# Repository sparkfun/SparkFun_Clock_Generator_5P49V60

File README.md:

SparkFun Clock Generator 5P49V60
========================================

[*SparkFun Clock Generator 5P49V60 (BOB-15734)*](https://www.sparkfun.com/products/15734)

The SparkFun Clock Generator 5P49V60 breakout board offers a wide range of customizable frequencies in a wide range 
of different signal types using a single reference clock. Four (single output) clock outputs can generate frequencies 
from 1MHz-200MHz and eight (differential output) clock outputs can generate frequencies from 1MHz-350MHz. The frequency's 
many properties can be manipulated in code via I2C using the SparkFun Arduino Library. The SparkFun Clock Generator also 
has four banks of programmable memory for the time when it's ready to sit on its' own within the project without a microcontroller.

Repository Contents
-------------------

* **/Hardware** - Eagle design files (.brd, .sch)
* **/Production** - Production panel files (.brd)
* **/Documentation** - Datasheet for the 5P49V60

Documentation
--------------
* **[Library](https://github.com/sparkfun/SparkFun_Clock_Generator_5P49V60_Arduino_Library)** - Arduino Library for the SparkFun Clock Generator 5P49V60
* **[Hookup Guide](https://learn.sparkfun.com/tutorials/sparkfun-clock-generator-5p49v60-qwiic-hookup-guide)** - Hookup Guide for the SparkFun Clock Generator 5P49V60
* **[SparkFun Fritzing repo](https://github.com/sparkfun/Fritzing_Parts)** - Fritzing diagrams for SparkFun products.

License Information
-------------------

This product is _**open source**_! 

Please review the LICENSE.md file for license information. 

If you have any questions or concerns on licensing, please contact technical support on our [SparkFun forums](https://forum.sparkfun.com/viewforum.php?f=152).

Distributed as-is; no warranty is given.

- Your friends at SparkFun.

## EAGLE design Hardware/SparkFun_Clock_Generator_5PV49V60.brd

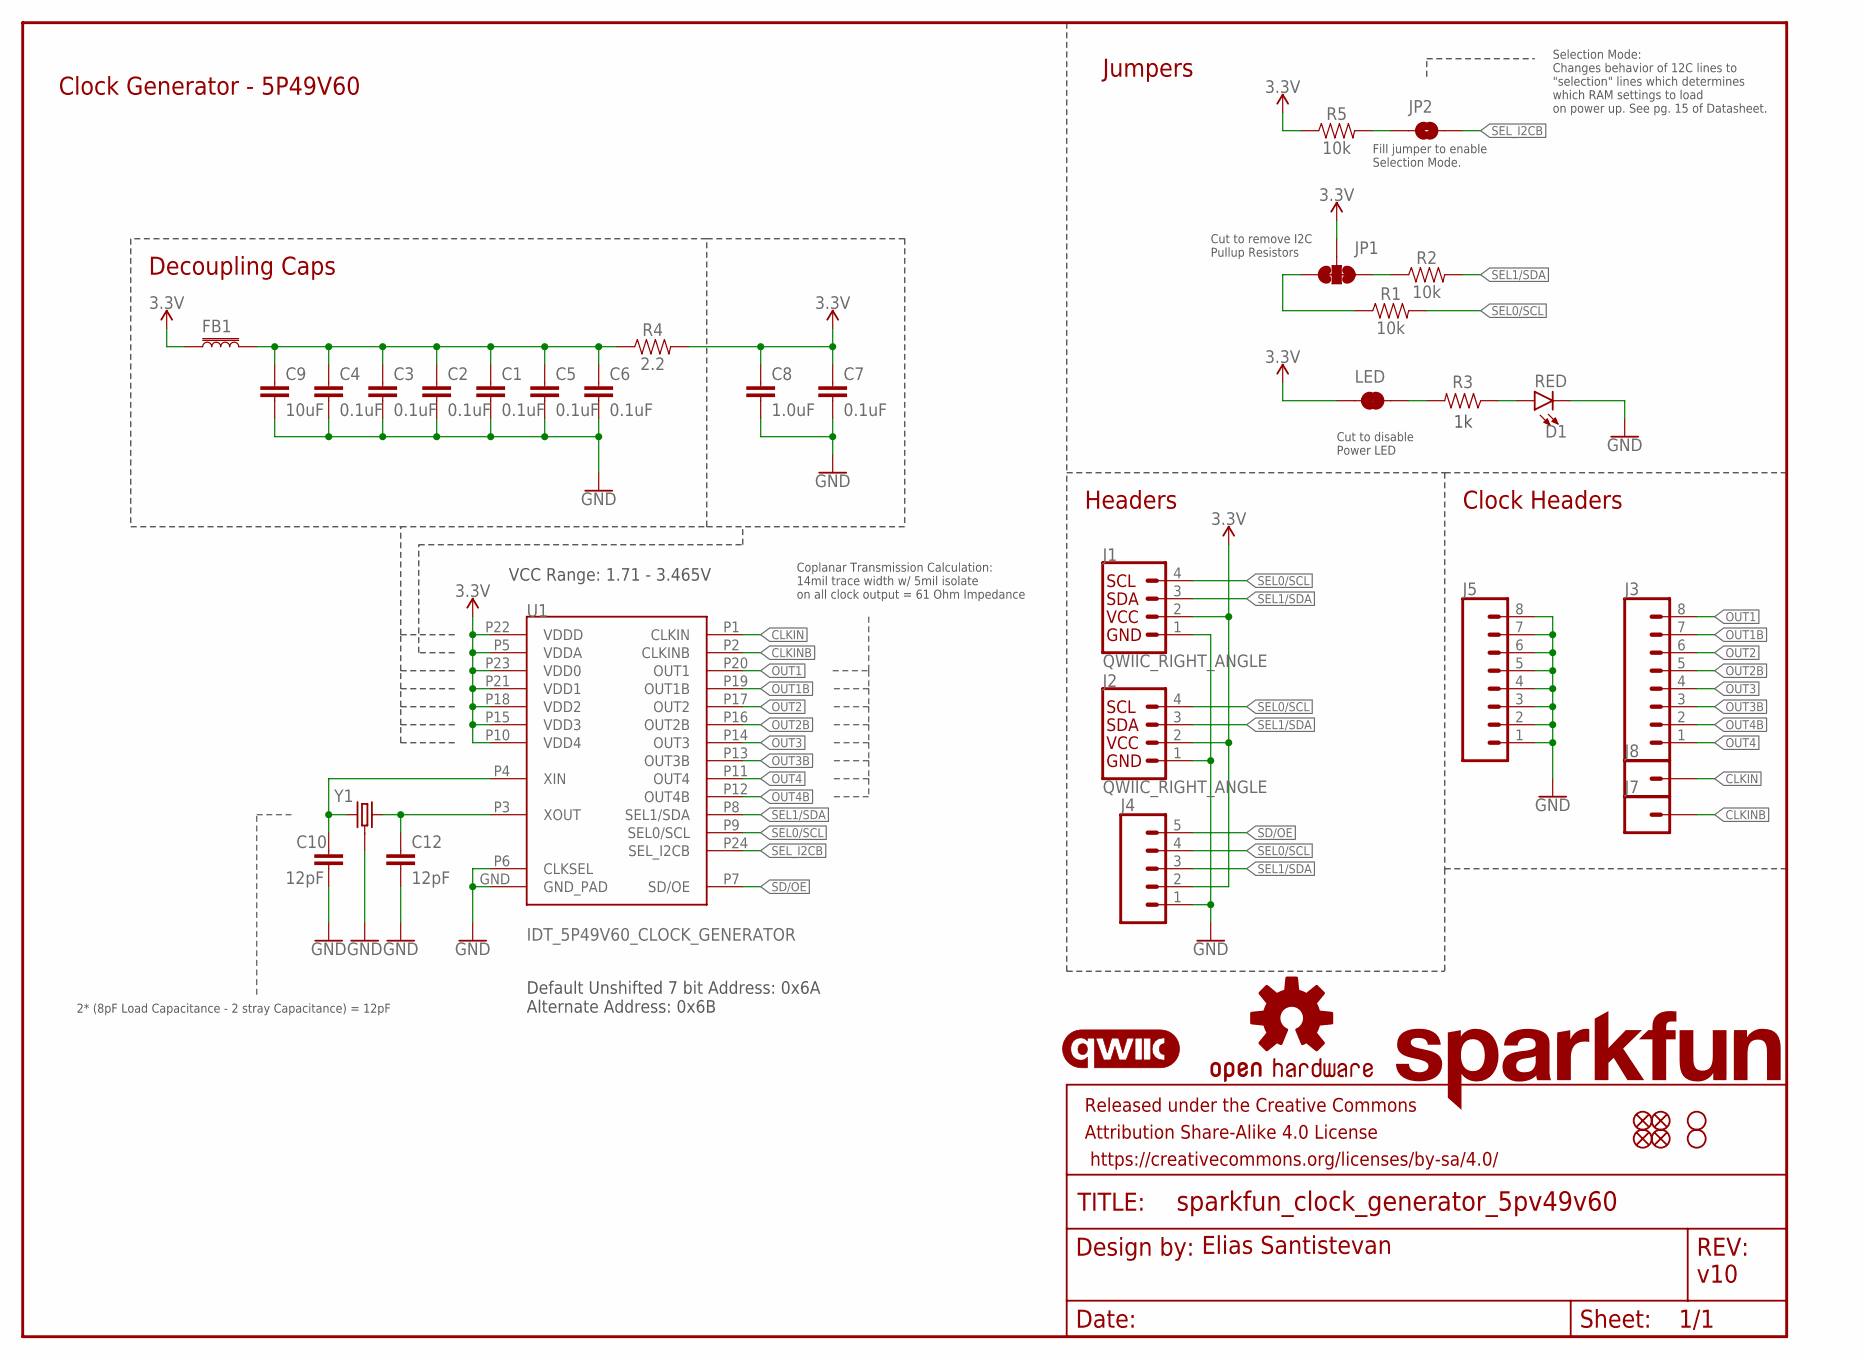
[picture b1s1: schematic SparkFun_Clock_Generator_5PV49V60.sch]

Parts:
C1, C2, C3, C4, C5, C6, C7: 0.1uF; 0402
C8: 1.0uF; 0402
C9: 10uF; 0603
C10, C12: 12pF; 0402
D1: RED; LED-0603
FB1: FERRITE_BEAD-120_OHM-0402; 0402
FD1, FD2, FD3, FD4: FIDUCIALUFIDUCIAL; FIDUCIAL-MICRO
FRAME1: FRAME-LETTER; CREATIVE_COMMONS
H1, H2: STAND-OFFTIGHT; STAND-OFF-TIGHT
J1, J2: QWIIC_RIGHT_ANGLE; JST04_1MM_RA
J3, J5: CONN_08NO_SILK_FEMALE_PTH; 1X08_NO_SILK
J4: CONN_05NO_SILK; 1X05_NO_SILK
J7, J8: CONN_01PTH_NO_SILK_SMALL; 1X01_SMALL
JP1: JUMPER-SMT_3_2-NC_TRACE_SILK; SMT-JUMPER_3_2-NC_TRACE_SILK
JP2: JUMPER-SMT_2_NO_SILK; SMT-JUMPER_2_NO_SILK
LED: JUMPER-SMT_2_NC_TRACE_SILK; SMT-JUMPER_2_NC_TRACE_SILK
LOGO1: SFE_LOGO_NAME.1_INCH; SFE_LOGO_NAME_.1
LOGO2: OSHW-LOGOS; OSHW-LOGO-S
LOGO3: QWIIC_LOGO_4MM; QWIIC_4MM
R1, R2, R5: 10k; 0402
R3: 1KOHM-0402-1/16W-1%; 0402
R4: 2.2; 0603
U1: IDT_5P49V60_CLOCK_GENERATOR; VFQFPN-24
Y1: 16MHz; CRYSTAL-SMD-2X2.5MM

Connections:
3.3V: C1.1, C2.1, C3.1, C4.1, C5.1, C6.1, C7.1, C8.1, C9.1, FB1.1, FB1.2, J1.2, J2.2, J4.2, JP1.2, LED.2, R4.1, R4.2, R5.1, U1.P5 (VDDA), U1.P10 (VDD4), U1.P15 (VDD3), U1.P18 (VDD2), U1.P21 (VDD1), U1.P22 (VDDD), U1.P23 (VDD0)
CLKIN: J8.P$1, U1.P1 (CLKIN)
CLKINB: J7.P$1, U1.P2 (CLKINB)
GND: C1.2, C2.2, C3.2, C4.2, C5.2, C6.2, C7.2, C8.2, C9.2, C10.2, C12.2, D1.C, J1.1, J2.1, J4.1, J5.1, J5.2, J5.3, J5.4, J5.5, J5.6, J5.7, J5.8, U1.GND (GND_PAD), U1.P6 (CLKSEL), Y1.P2 (GND), Y1.P4 (GND)
unnamed: JP1.1, R2.1
unnamed: C12.1, U1.P3 (XOUT), Y1.P1 (1)
unnamed: JP1.3, R1.1
unnamed: LED.1, R3.2
unnamed: D1.A, R3.1
unnamed: C10.1, U1.P4 (XIN), Y1.P3 (2)
unnamed: JP2.1, R5.2
OUT1: J3.8, U1.P20 (OUT1)
OUT1B: J3.7, U1.P19 (OUT1B)
OUT2: J3.6, U1.P17 (OUT2)
OUT2B: J3.5, U1.P16 (OUT2B)
OUT3: J3.4, U1.P14 (OUT3)
OUT3B: J3.3, U1.P13 (OUT3B)
OUT4: J3.1, U1.P11 (OUT4)
OUT4B: J3.2, U1.P12 (OUT4B)
SD/OE: J4.5, U1.P7 (SD/OE)
SEL0/SCL: J1.4, J2.4, J4.4, R1.2, U1.P9 (SEL0/SCL)
SEL1/SDA: J1.3, J2.3, J4.3, R2.2, U1.P8 (SEL1/SDA)
SEL_I2CB: JP2.2, U1.P24 (SEL_I2CB)

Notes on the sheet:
Elias Santistevan
v10
Clock Generator - 5P49V60
Jumpers
Headers
Clock Headers
Decoupling Caps
Cut to remove I2C Pullup Resistors
Cut to disable Power LED
VCC Range: 1.71 - 3.465V
Default Unshifted 7 bit Address: 0x6A Alternate Address: 0x6B
Fill jumper to enable Selection Mode.
Selection Mode: Changes behavior of 12C lines to "selection" lines which determines which RAM settings to load on power up. See pg. 15 of Datasheet.
Coplanar Transmission Calculation: 14mil trace width w/ 5mil isolate on all clock output = 61 Ohm Impedance
2* (8pF Load Capacitance - 2 stray Capacitance) = 12pF

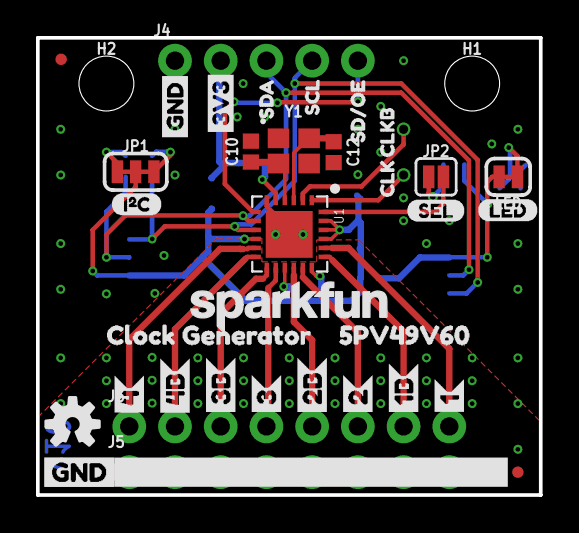
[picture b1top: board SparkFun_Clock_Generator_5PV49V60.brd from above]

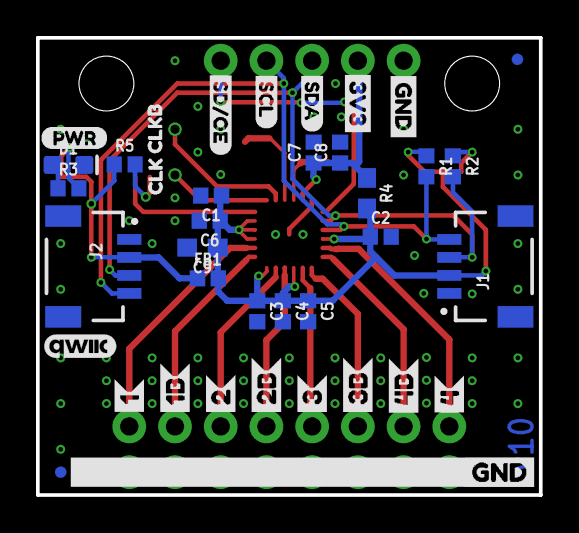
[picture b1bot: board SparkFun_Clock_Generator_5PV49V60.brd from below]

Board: 2 copper layers, 27.9 x 25.4 mm, 78 parts (38 on the bottom side), 23 nets.

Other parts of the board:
U$1: SEL0
U$2, U$18: 3V3-03
U$3, U$19: GND-03
U$4: PWR-()-03
U$5: SDA11
U$6: SCL10
U$7: SD#OE12
U$8, U$38: 46
U$9, U$25: 4B7
U$10, U$24: 3B5
U$11, U$37: 34
U$12, U$23: 2B3
U$13, U$27: 22
U$14, U$22: 1B1
U$15, U$26: 10
U$16: CLOCK_GENERATOR0
U$17: 5PV49V601
U$20, U$21: GND-04
U$28: SCL1
U$29: SD#OE2
U$30: SDA0
U$31, U$33: CLK12
U$32, U$34: CLKB13
U$35: I_SUPER2_C-()-03
U$36: LED0

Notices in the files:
parts and their libraries:
SparkFun-Aesthetics: Licensing: Creative Commons ShareAlike 4.0 International - https://creativecommons.org/licenses/by-sa/4.0
SparkFun-Aesthetics: Released under the Creative Commons Attribution Share-Alike 4.0 License
SparkFun-Aesthetics: https://creativecommons.org/licenses/by-sa/4.0
